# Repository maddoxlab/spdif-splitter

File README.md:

# spdif-splitter
Design files and code for S/Plitter, a box that turns optical S/PDIF signals into separate TTL bits for EEG triggering in auditory experiments

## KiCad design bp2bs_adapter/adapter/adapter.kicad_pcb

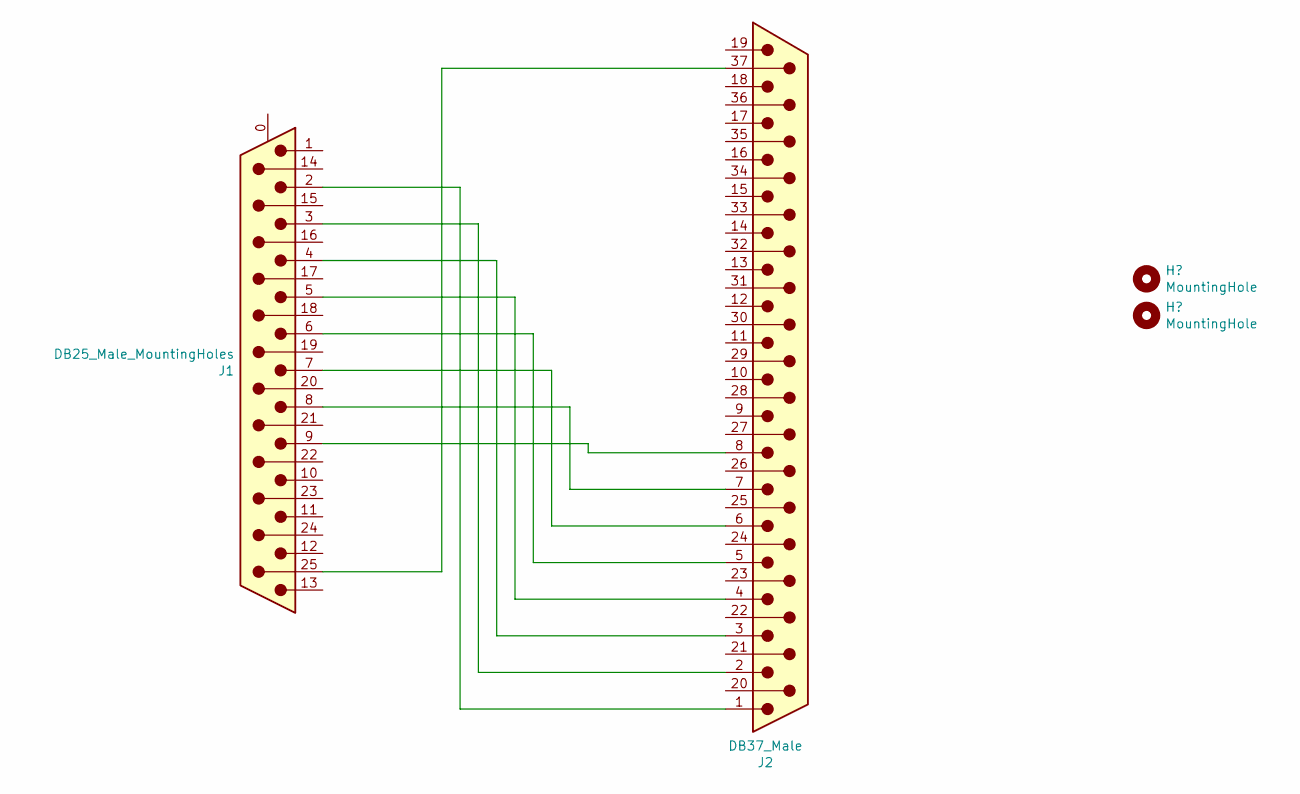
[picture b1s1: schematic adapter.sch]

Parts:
J1: DB25_Male_MountingHoles; DSUB-25_Male_Horizontal_P2.77x2.84mm_EdgePinOffset4.94mm_Ho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
J2: DB37_Male; DSUB-37_Male_Horizontal_P2.77x2.84mm_EdgePinOffset7.70mm_Ho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

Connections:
unnamed: J1.2, J2.1
unnamed: J1.3, J2.2
unnamed: J1.4, J2.3
unnamed: J1.5, J2.4
unnamed: J1.6, J2.5
unnamed: J1.7, J2.6
unnamed: J1.8, J2.7
unnamed: J1.9, J2.8
unnamed: J1.25, J2.37

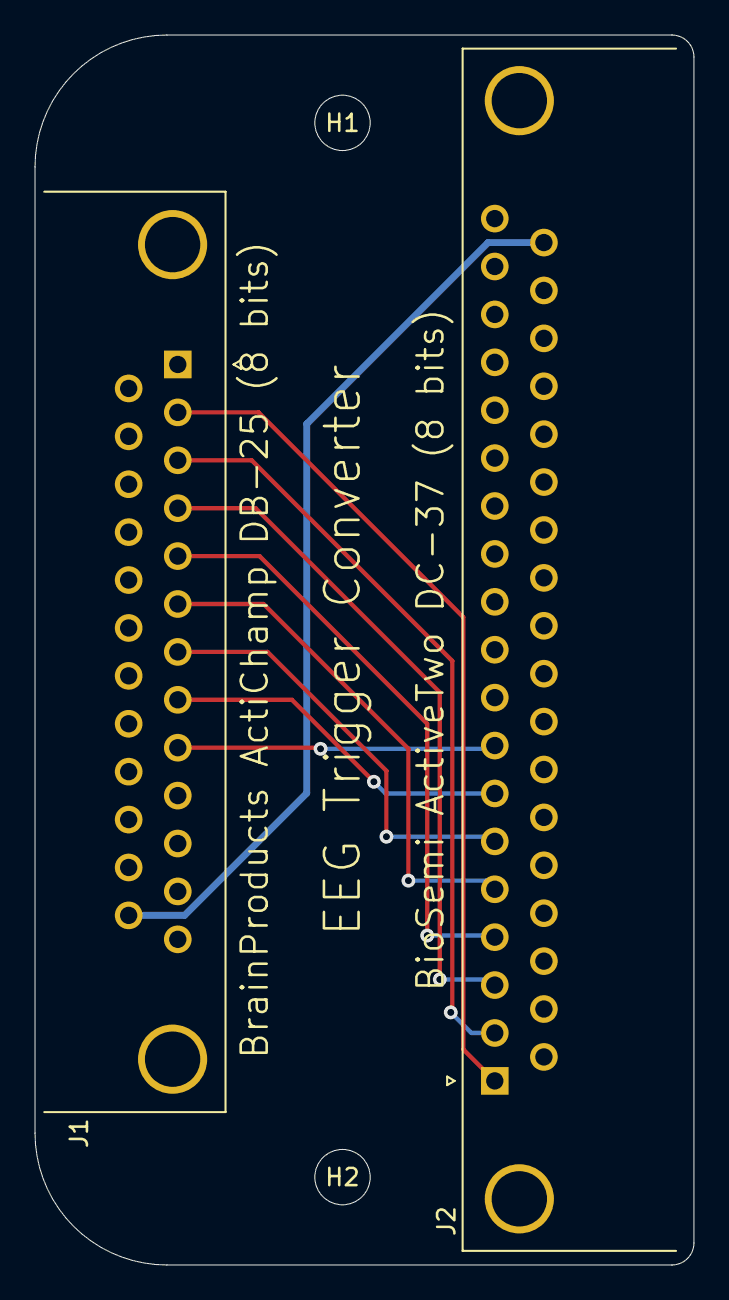
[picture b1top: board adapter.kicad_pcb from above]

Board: 2 copper layers, 38.1 x 71.1 mm, 4 parts (0 on the bottom side), 9 nets.

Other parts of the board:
H1, H2: MountingHole; MountingHole_3.2mm_M3

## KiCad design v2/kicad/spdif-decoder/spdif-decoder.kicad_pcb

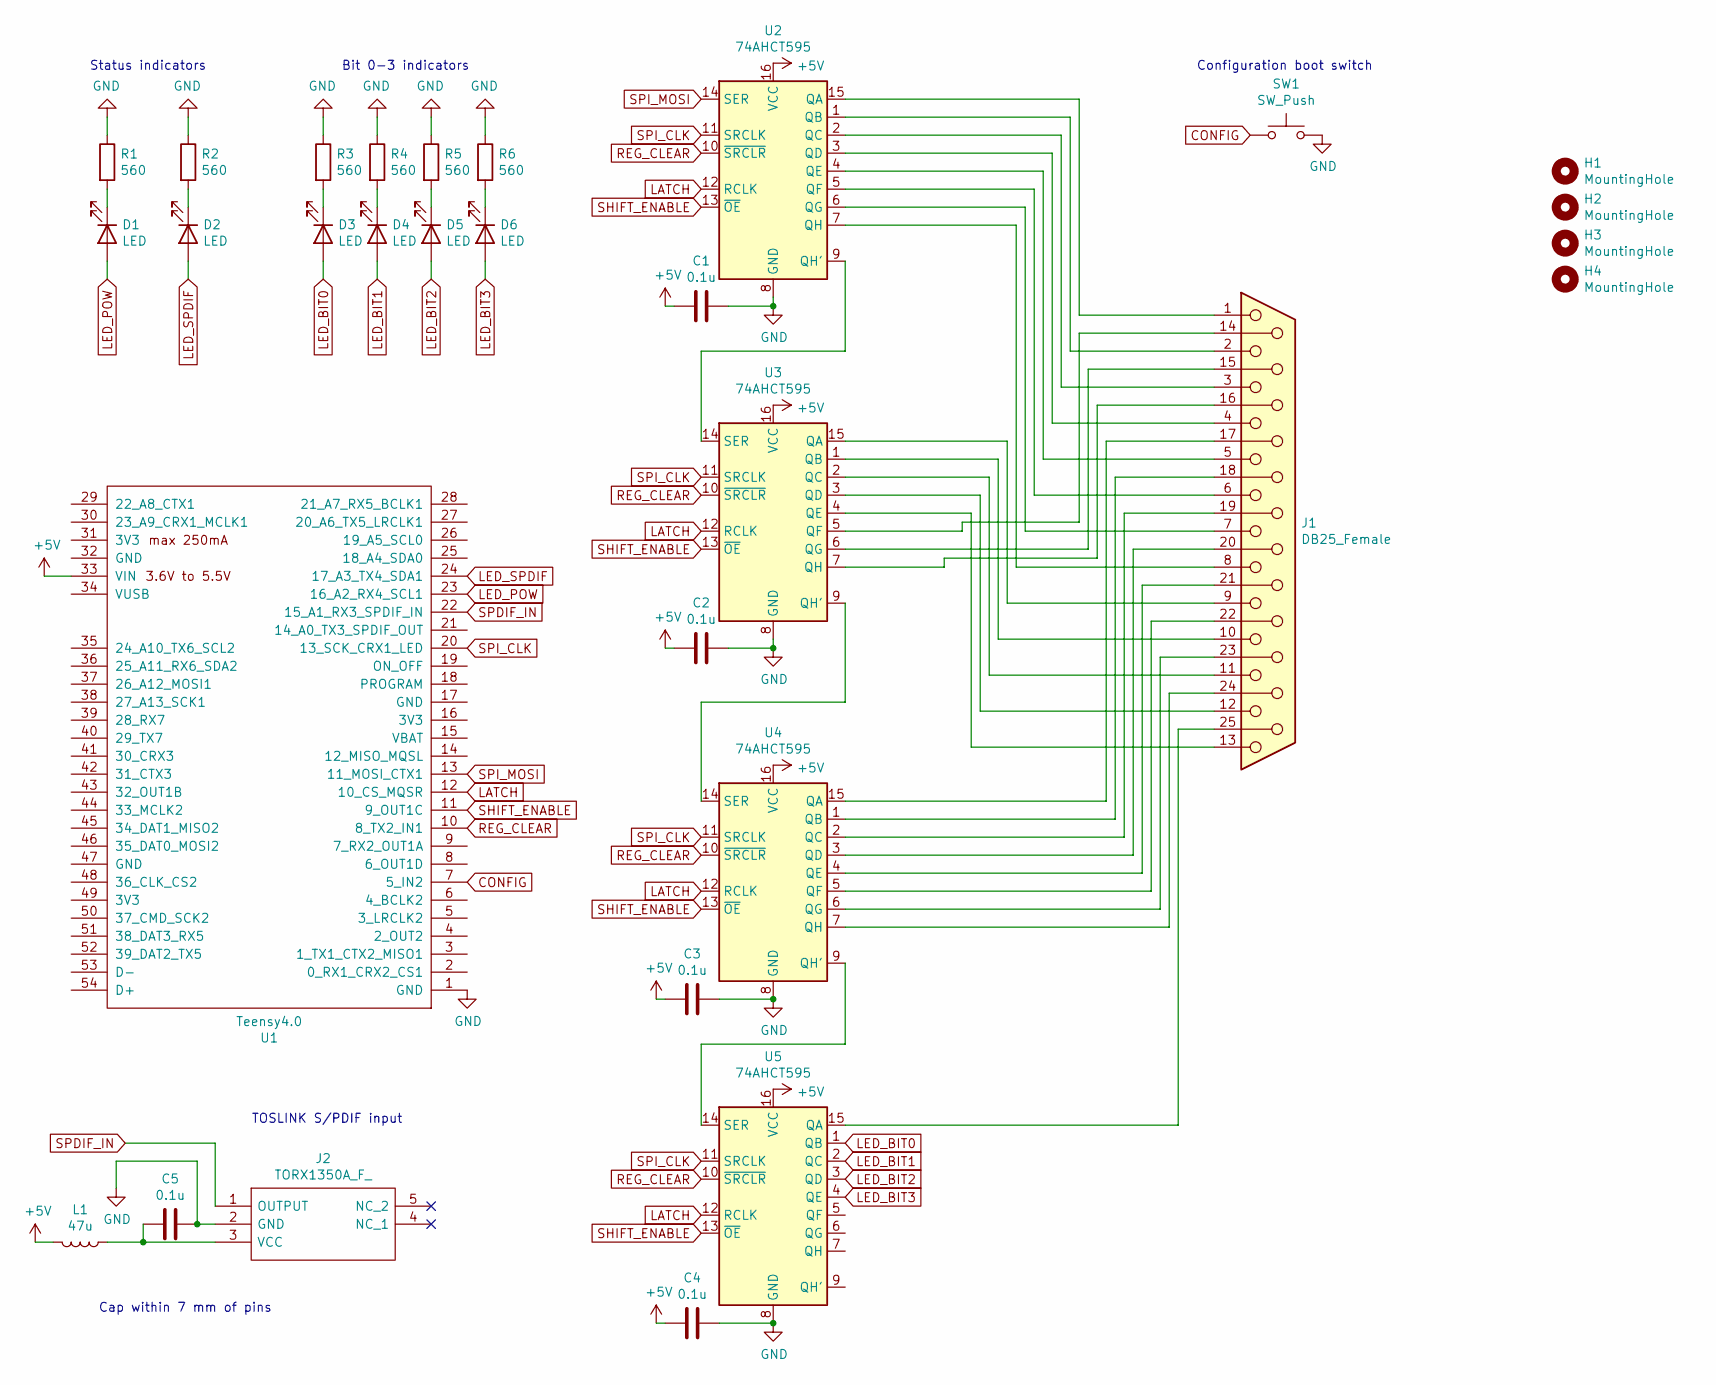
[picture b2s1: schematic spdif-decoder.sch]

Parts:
C1, C2, C3, C4, C5: 0.1u; C_Disc_D3.0mm_W2.0mm_P2.50mm
D1, D2, D3, D4, D5, D6: LED; LED_D3.0mm
H1, H2, H3, H4: MountingHole; MountingHole_3.2mm_M3
J1: DB25_Female; DSUB-25_Female_Horizontal_P2.77x2.84mm_EdgePinOffset9.90mm_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
J2: TORX1350A_F_; TORX1350AF; Mouser Part Number 757-TORX1350AF
L1: 47u; L_Axial_L5.3mm_D2.2mm_P2.54mm_Vertical_Vishay_IM-1
R1, R2, R3, R4, R5, R6: 560; R_Axial_DIN0207_L6.3mm_D2.5mm_P7.62mm_Horizontal
SW1: SW_Push; SW_PUSH_6mm
U1: Teensy4.0; Teensy40
U2, U3, U4, U5: 74AHCT595; DIP-16_W7.62mm

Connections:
+5V: C1.2, C2.2, C3.2, C4.2, L1.2, U1.33 (VIN), U2.16 (VCC), U3.16 (VCC), U4.16 (VCC), U5.16 (VCC)
CONFIG: SW1.1, U1.7 (5_IN2)
GND: C1.1, C2.1, C3.1, C4.1, C5.1, J2.2 (GND), R1.1, R2.1, R3.1, R4.1, R5.1, R6.1, SW1.2, U1.1 (GND), U2.8 (GND), U3.8 (GND), U4.8 (GND), U5.8 (GND)
LATCH: U1.12 (10_CS_MQSR), U2.12 (RCLK), U3.12 (RCLK), U4.12 (RCLK), U5.12 (RCLK)
LED_BIT0: D3.2 (A), U5.1 (QB)
LED_BIT1: D4.2 (A), U5.2 (QC)
LED_BIT2: D5.2 (A), U5.3 (QD)
LED_BIT3: D6.2 (A), U5.4 (QE)
LED_POW: D1.2 (A), U1.23 (16_A2_RX4_SCL1)
LED_SPDIF: D2.2 (A), U1.24 (17_A3_TX4_SDA1)
unnamed: C5.2, J2.3 (VCC), L1.1
unnamed: D1.1 (K), R1.2
unnamed: D2.1 (K), R2.2
unnamed: D3.1 (K), R3.2
unnamed: D4.1 (K), R4.2
unnamed: D5.1 (K), R5.2
unnamed: D6.1 (K), R6.2
unnamed: J1.1, U2.15 (QA)
unnamed: J1.2, U2.1 (QB)
unnamed: J1.3, U2.2 (QC)
unnamed: J1.4, U2.3 (QD)
unnamed: J1.5, U2.4 (QE)
unnamed: J1.6, U2.5 (QF)
unnamed: J1.7, U2.6 (QG)
unnamed: J1.8, U2.7 (QH)
unnamed: J1.9, U3.15 (QA)
unnamed: J1.10, U3.1 (QB)
unnamed: J1.11, U3.2 (QC)
unnamed: J1.12, U3.3 (QD)
unnamed: J1.13, U3.4 (QE)
unnamed: J1.14, U3.5 (QF)
unnamed: J1.15, U3.6 (QG)
unnamed: J1.16, U3.7 (QH)
unnamed: J1.17, U4.15 (QA)
unnamed: J1.18, U4.1 (QB)
unnamed: J1.19, U4.2 (QC)
unnamed: J1.20, U4.3 (QD)
unnamed: J1.21, U4.4 (QE)
unnamed: J1.22, U4.5 (QF)
unnamed: J1.23, U4.6 (QG)
unnamed: J1.24, U4.7 (QH)
unnamed: J1.25, U5.15 (QA)
unnamed: U2.9 (QH'), U3.14 (SER)
unnamed: U3.9 (QH'), U4.14 (SER)
unnamed: U4.9 (QH'), U5.14 (SER)
REG_CLEAR: U1.10 (8_TX2_IN1), U2.10 (~SRCLR), U3.10 (~SRCLR), U4.10 (~SRCLR), U5.10 (~SRCLR)
SHIFT_ENABLE: U1.11 (9_OUT1C), U2.13 (~OE), U3.13 (~OE), U4.13 (~OE), U5.13 (~OE)
SPDIF_IN: J2.1 (OUTPUT), U1.22 (15_A1_RX3_SPDIF_IN)
SPI_CLK: U1.20 (13_SCK_CRX1_LED), U2.11 (SRCLK), U3.11 (SRCLK), U4.11 (SRCLK), U5.11 (SRCLK)
SPI_MOSI: U1.13 (11_MOSI_CTX1), U2.14 (SER)

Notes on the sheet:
Bit 0-3 indicators
Status indicators
TOSLINK S/PDIF input
Cap within 7 mm of pins
Configuration boot switch

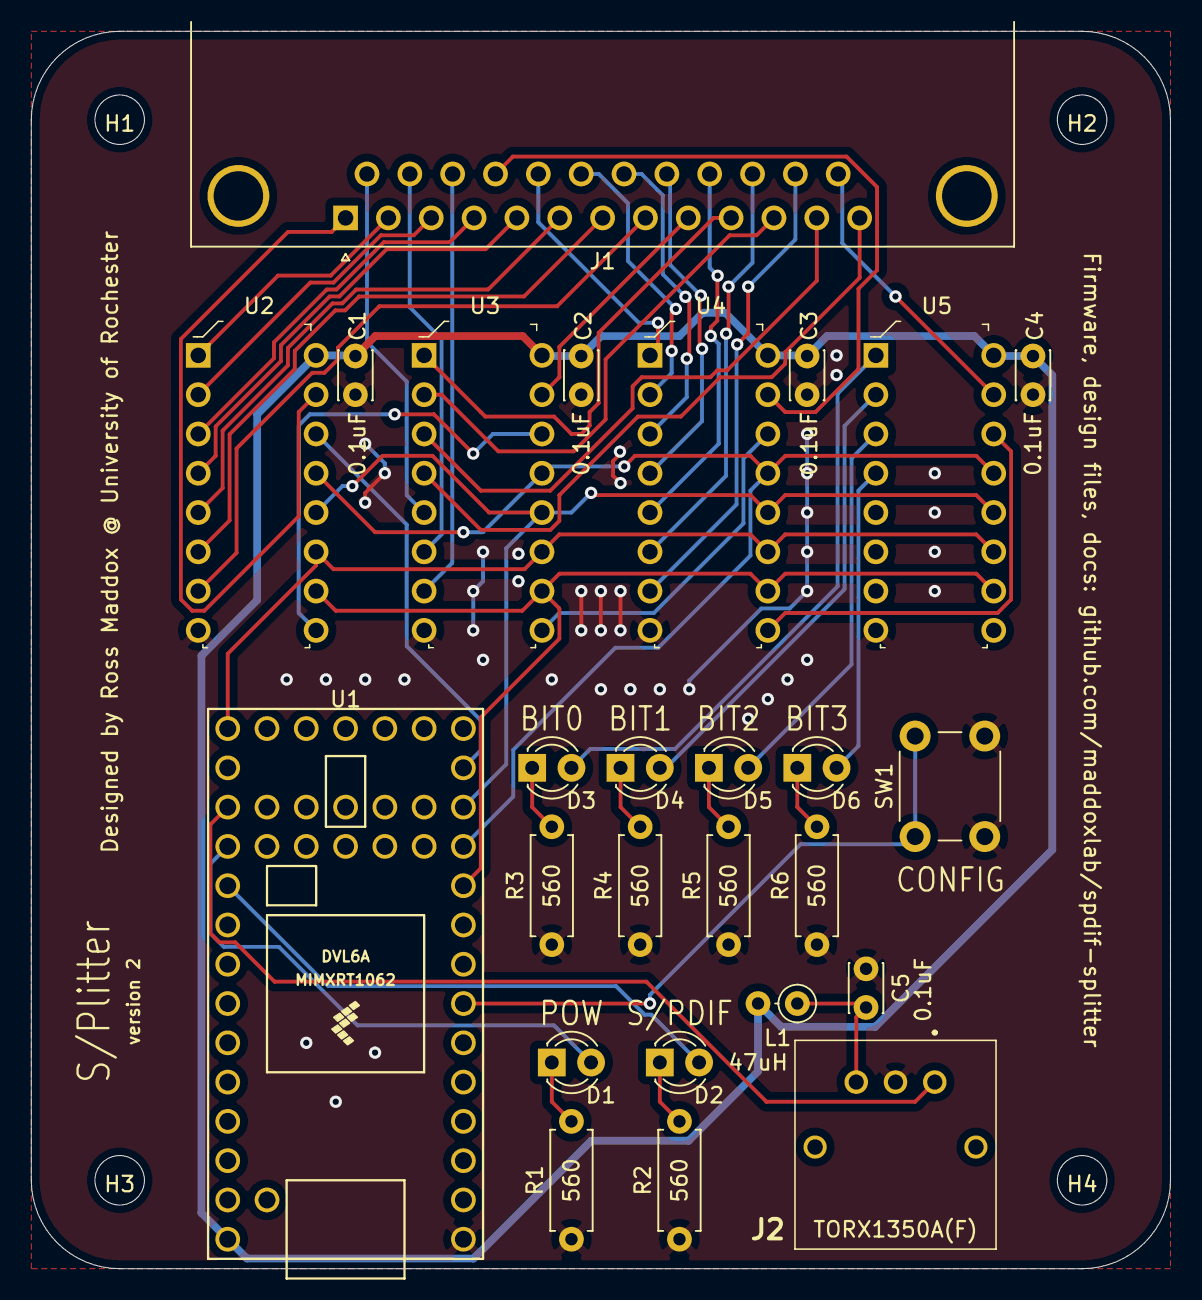
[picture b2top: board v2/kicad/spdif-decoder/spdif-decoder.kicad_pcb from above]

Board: 2 copper layers, 73.7 x 80.0 mm, 30 parts (0 on the bottom side), 50 nets.

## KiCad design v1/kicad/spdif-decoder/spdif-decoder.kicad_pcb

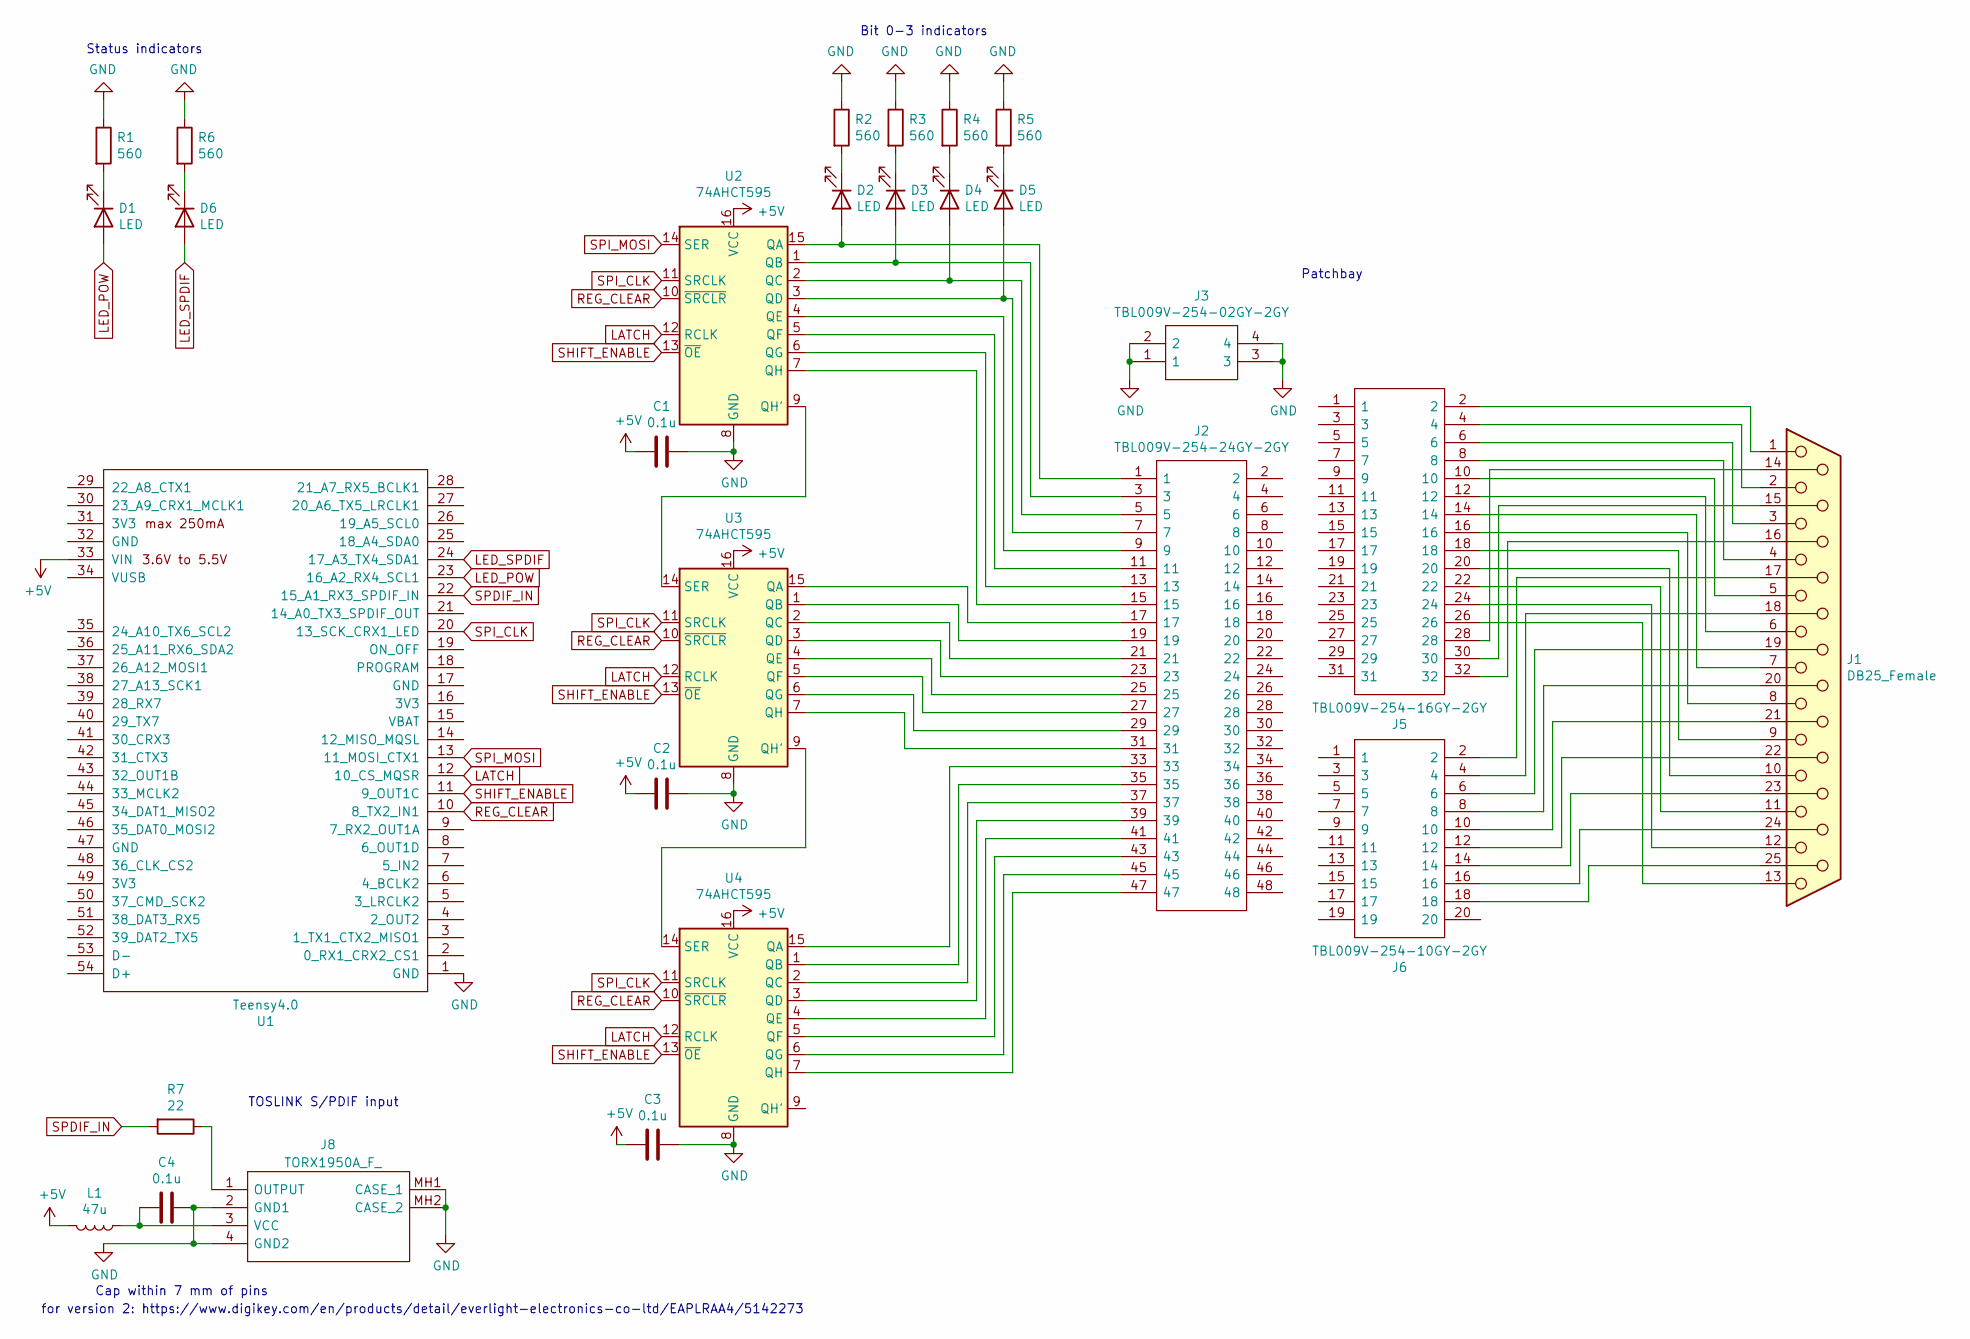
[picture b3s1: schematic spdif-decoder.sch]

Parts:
C1, C2, C3, C4: 0.1u; C_Disc_D3.0mm_W2.0mm_P2.50mm
D1, D2, D3, D4, D5, D6: LED; LED_D3.0mm
J1: DB25_Female; DSUB-25_Female_Horizontal_P2.77x2.84mm_EdgePinOffset9.40mm
J2: TBL009V-254-24GY-2GY; TBL009V25424GY2GY; Mouser Part Number 490-TBL09V25424GY2GY
J3: TBL009V-254-02GY-2GY; TBL009V25402GY2GY; Mouser Part Number 490-TBL09V25402GY2GY
J5: TBL009V-254-16GY-2GY; TBL009V25416GY2GY; Mouser Part Number 490-TBL09V25416GY2GY
J6: TBL009V-254-10GY-2GY; TBL009V25410GY2GY; Mouser Part Number 490-TBL09V25410GY2GY
J8: TORX1950A_F_; TORX1950AF; Mouser Part Number 71-TORX1950A(F)
L1: 47u; L_Axial_L5.3mm_D2.2mm_P2.54mm_Vertical_Vishay_IM-1
R1, R2, R3, R4, R5, R6: 560; R_Axial_DIN0207_L6.3mm_D2.5mm_P7.62mm_Horizontal
R7: 22; R_Axial_DIN0207_L6.3mm_D2.5mm_P7.62mm_Horizontal
U1: Teensy4.0; Teensy40
U2, U3, U4: 74AHCT595; DIP-16_W7.62mm

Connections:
+5V: C1.2, C2.2, C3.2, L1.2, U1.33 (VIN), U2.16 (VCC), U3.16 (VCC), U4.16 (VCC)
GND: C1.1, C2.1, C3.1, C4.1, J3.1, J3.2, J3.3, J3.4, J8.2 (GND1), J8.4 (GND2), J8.MH1 (CASE_1), J8.MH2 (CASE_2), R1.1, R2.1, R3.1, R4.1, R5.1, R6.1, U1.1 (GND), U2.8 (GND), U3.8 (GND), U4.8 (GND)
LATCH: U1.12 (10_CS_MQSR), U2.12 (RCLK), U3.12 (RCLK), U4.12 (RCLK)
LED_POW: D1.2 (A), U1.23 (16_A2_RX4_SCL1)
LED_SPDIF: D6.2 (A), U1.24 (17_A3_TX4_SDA1)
unnamed: C4.2, J8.3 (VCC), L1.1
unnamed: D1.1 (K), R1.2
unnamed: D2.1 (K), R2.2
unnamed: D2.2 (A), J2.1, U2.15 (QA)
unnamed: D3.1 (K), R3.2
unnamed: D3.2 (A), J2.3, U2.1 (QB)
unnamed: D4.1 (K), R4.2
unnamed: D4.2 (A), J2.5, U2.2 (QC)
unnamed: D5.1 (K), R5.2
unnamed: D5.2 (A), J2.7, U2.3 (QD)
unnamed: D6.1 (K), R6.2
unnamed: J1.1, J5.2
unnamed: J1.2, J5.4
unnamed: J1.3, J5.6
unnamed: J1.4, J5.8
unnamed: J1.5, J5.10
unnamed: J1.6, J5.12
unnamed: J1.7, J5.14
unnamed: J1.8, J5.16
unnamed: J1.9, J5.18
unnamed: J1.10, J5.20
unnamed: J1.11, J5.22
unnamed: J1.12, J5.24
unnamed: J1.13, J5.26
unnamed: J1.14, J5.28
unnamed: J1.15, J5.30
unnamed: J1.16, J5.32
unnamed: J1.17, J6.2
unnamed: J1.18, J6.4
unnamed: J1.19, J6.6
unnamed: J1.20, J6.8
unnamed: J1.21, J6.10
unnamed: J1.22, J6.12
unnamed: J1.23, J6.14
unnamed: J1.24, J6.16
unnamed: J1.25, J6.18
unnamed: J2.9, U2.4 (QE)
unnamed: J2.11, U2.5 (QF)
unnamed: J2.13, U2.6 (QG)
unnamed: J2.15, U2.7 (QH)
unnamed: J2.17, U3.15 (QA)
unnamed: J2.19, U3.1 (QB)
unnamed: J2.21, U3.2 (QC)
unnamed: J2.23, U3.3 (QD)
unnamed: J2.25, U3.4 (QE)
unnamed: J2.27, U3.5 (QF)
unnamed: J2.29, U3.6 (QG)
unnamed: J2.31, U3.7 (QH)
unnamed: J2.33, U4.15 (QA)
unnamed: J2.35, U4.1 (QB)
unnamed: J2.37, U4.2 (QC)
unnamed: J2.39, U4.3 (QD)
unnamed: J2.41, U4.4 (QE)
unnamed: J2.43, U4.5 (QF)
unnamed: J2.45, U4.6 (QG)
unnamed: J2.47, U4.7 (QH)
unnamed: J8.1 (OUTPUT), R7.1
unnamed: U2.9 (QH'), U3.14 (SER)
unnamed: U3.9 (QH'), U4.14 (SER)
REG_CLEAR: U1.10 (8_TX2_IN1), U2.10 (~SRCLR), U3.10 (~SRCLR), U4.10 (~SRCLR)
SHIFT_ENABLE: U1.11 (9_OUT1C), U2.13 (~OE), U3.13 (~OE), U4.13 (~OE)
SPDIF_IN: R7.2, U1.22 (15_A1_RX3_SPDIF_IN)
SPI_CLK: U1.20 (13_SCK_CRX1_LED), U2.11 (SRCLK), U3.11 (SRCLK), U4.11 (SRCLK)
SPI_MOSI: U1.13 (11_MOSI_CTX1), U2.14 (SER)

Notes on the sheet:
Cap within 7 mm of pins
Bit 0-3 indicators
Status indicators
Patchbay
for version 2: https://www.digikey.com/en/products/detail/everlight-electronics-co-ltd/EAPLRAA4/5142273
TOSLINK S/PDIF input

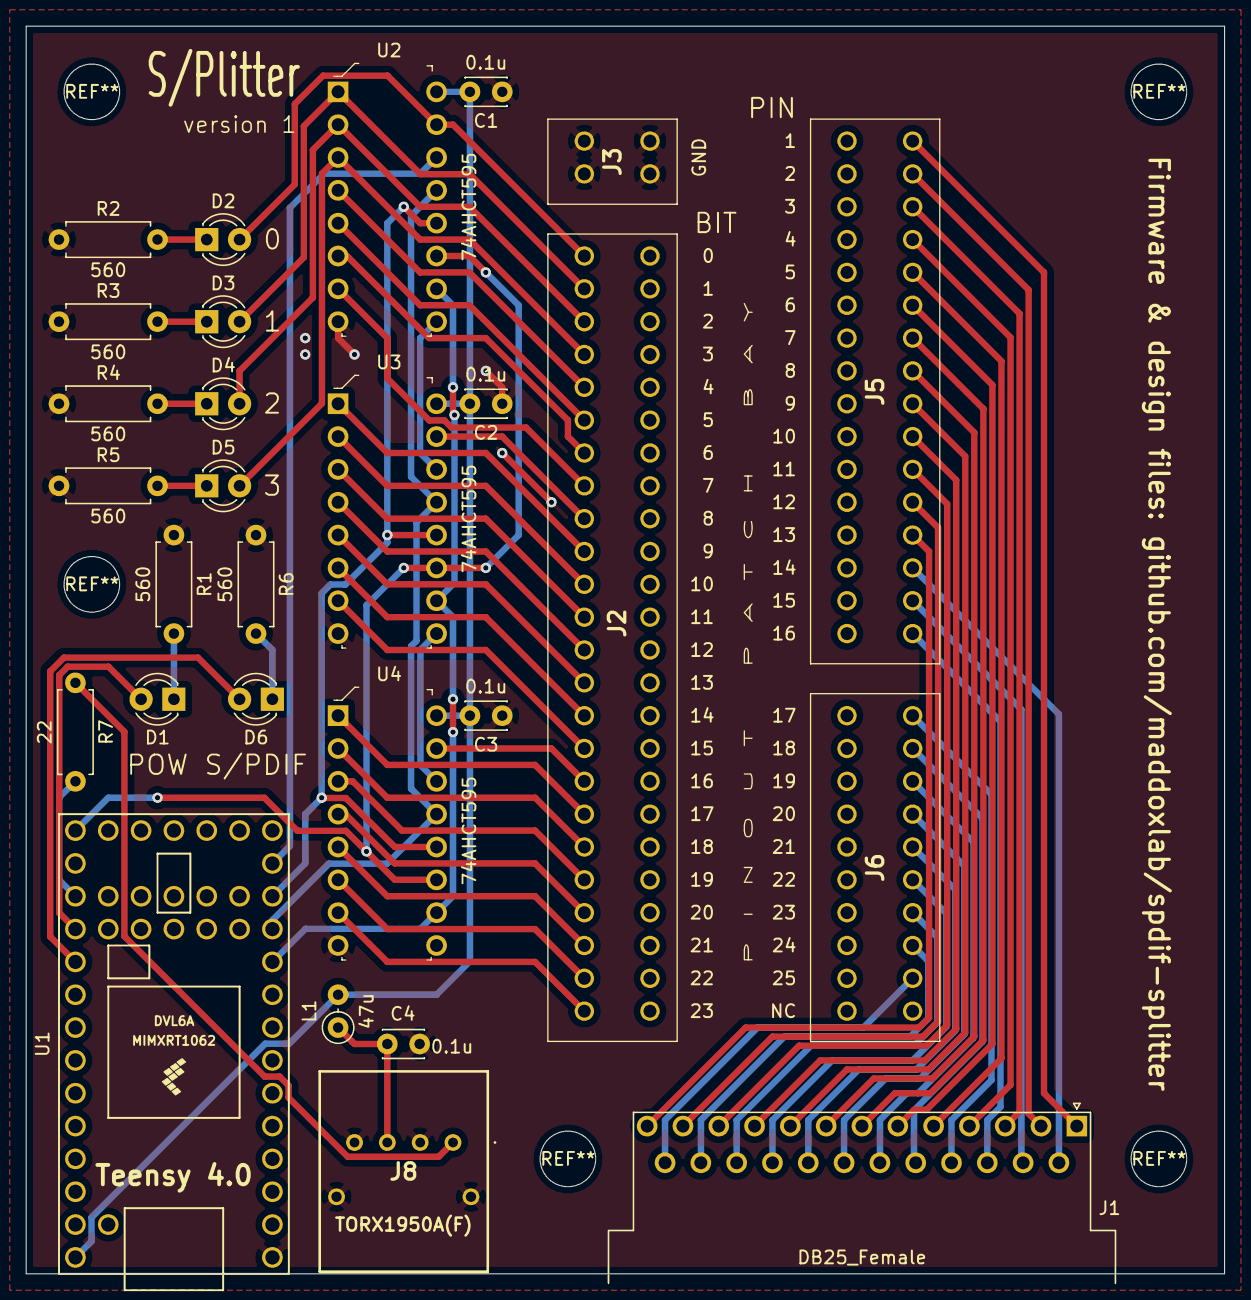
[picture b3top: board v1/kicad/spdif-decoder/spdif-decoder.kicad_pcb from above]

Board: 2 copper layers, 92.7 x 96.5 mm, 28 parts (0 on the bottom side), 69 nets.

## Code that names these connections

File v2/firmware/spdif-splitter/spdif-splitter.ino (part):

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#define SPDIF_PIN_MODE 3

// Set some pin names
#define CONFIG_PIN 5
#define REG_CLEAR_PIN 8
#define SHIFT_ENABLE_PIN 9
#define LATCH_PIN 10
#define SPI_MOSI_PIN 11
#define SPI_CLK_PIN 13
#define LED_POW_PIN 16
#define LED_SPDIF_PIN 17

// adresses in which the pinout bytes are stored -- 4 bytes needed for 25 pins
// each bit of pinout corresponds to a pin and the value stored says which bit to write
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  IOMUXC_SPDIF_IN_SELECT_INPUT = 0; // GPIO_AD_B1_03_ALT3 - taken from input_spdif

  // Set up SPI shift registers ========
  pinMode(CONFIG_PIN, INPUT_PULLUP);
  pinMode(LATCH_PIN, OUTPUT);
  pinMode(SHIFT_ENABLE_PIN, OUTPUT);
  pinMode(REG_CLEAR_PIN, OUTPUT);
  pinMode(LED_POW_PIN, OUTPUT);
  pinMode(LED_SPDIF_PIN, OUTPUT);

  // Interactively set the pinout if the config pin was held down at boot ========
  if (digitalReadFast(CONFIG_PIN) == LOW) {
    config();
  }

  digitalWriteFast(SHIFT_ENABLE_PIN, LOW); // enable low
  digitalWriteFast(REG_CLEAR_PIN, LOW); // clear low
  digitalWriteFast(REG_CLEAR_PIN, HIGH); // clear low
  digitalWriteFast(LED_POW_PIN, HIGH);
  SPI.begin();

  // Read in all the pinout information ========
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      out_bits |= (spdif_fifo_current & 0b1111) << (n_pins); // LED indicators show first four bits

      SPI.beginTransaction(SPISettings(100000000, MSBFIRST, SPI_MODE0));
      digitalWriteFast(LATCH_PIN, LOW);
      SPI.transfer(byte(out_bits >> 24));
      SPI.transfer(byte(out_bits >> 16));
      SPI.transfer(byte(out_bits >> 8));
      SPI.transfer(byte(out_bits >> 0));
      digitalWriteFast(LATCH_PIN, HIGH);
      SPI.endTransaction();

      spdif_fifo_prior = spdif_fifo_current;
    }
  } else { // zero everything out if SPDIF is not connected
    SPI.beginTransaction(SPISettings(100000000, MSBFIRST, SPI_MODE0));
    digitalWriteFast(LATCH_PIN, LOW);

    SPI.transfer(0); // this should really just use a clear instead
    SPI.transfer(0);
    SPI.transfer(0);
    SPI.transfer(0);

    digitalWriteFast(LATCH_PIN, HIGH);
    SPI.endTransaction();

    spdif_fifo_prior = 0;
  }

  digitalWriteFast(LED_SPDIF_PIN, spdif_locked);
}

void config() {
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  char choice;
  const byte *pinout_choice ;
  
  digitalWriteFast(LED_POW_PIN, LOW);
  digitalWriteFast(LED_SPDIF_PIN, HIGH);

  // Set the input audio channel
  Serial.println("Your pinout options are: ");
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
  for (unsigned int i = 0; i < 10; i++) { // Flash the lights to know that config was successful
    delay(100);
    digitalWriteFast(LED_POW_PIN, HIGH);
    digitalWriteFast(LED_SPDIF_PIN, LOW);
    delay(100);
    digitalWriteFast(LED_POW_PIN, LOW);
    digitalWriteFast(LED_SPDIF_PIN, HIGH);
  }
}

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
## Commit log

2021-08-16 add inital files
2021-08-16 improve firmware
    removed commented out stuff, zero everything out if
2021-08-18 add v2
2021-08-18 mods, case
2021-09-04 working maybe?
2021-09-14 adapter
2023-03-24 Update spdif-splitter.ino
    Fix SPDIF FIFO read in v2
2023-03-30 Update spdif-splitter.ino
    Fixed OOO error with parentheses
2023-04-20 Update spdif-splitter.ino
    Minor tweaks in config menu
